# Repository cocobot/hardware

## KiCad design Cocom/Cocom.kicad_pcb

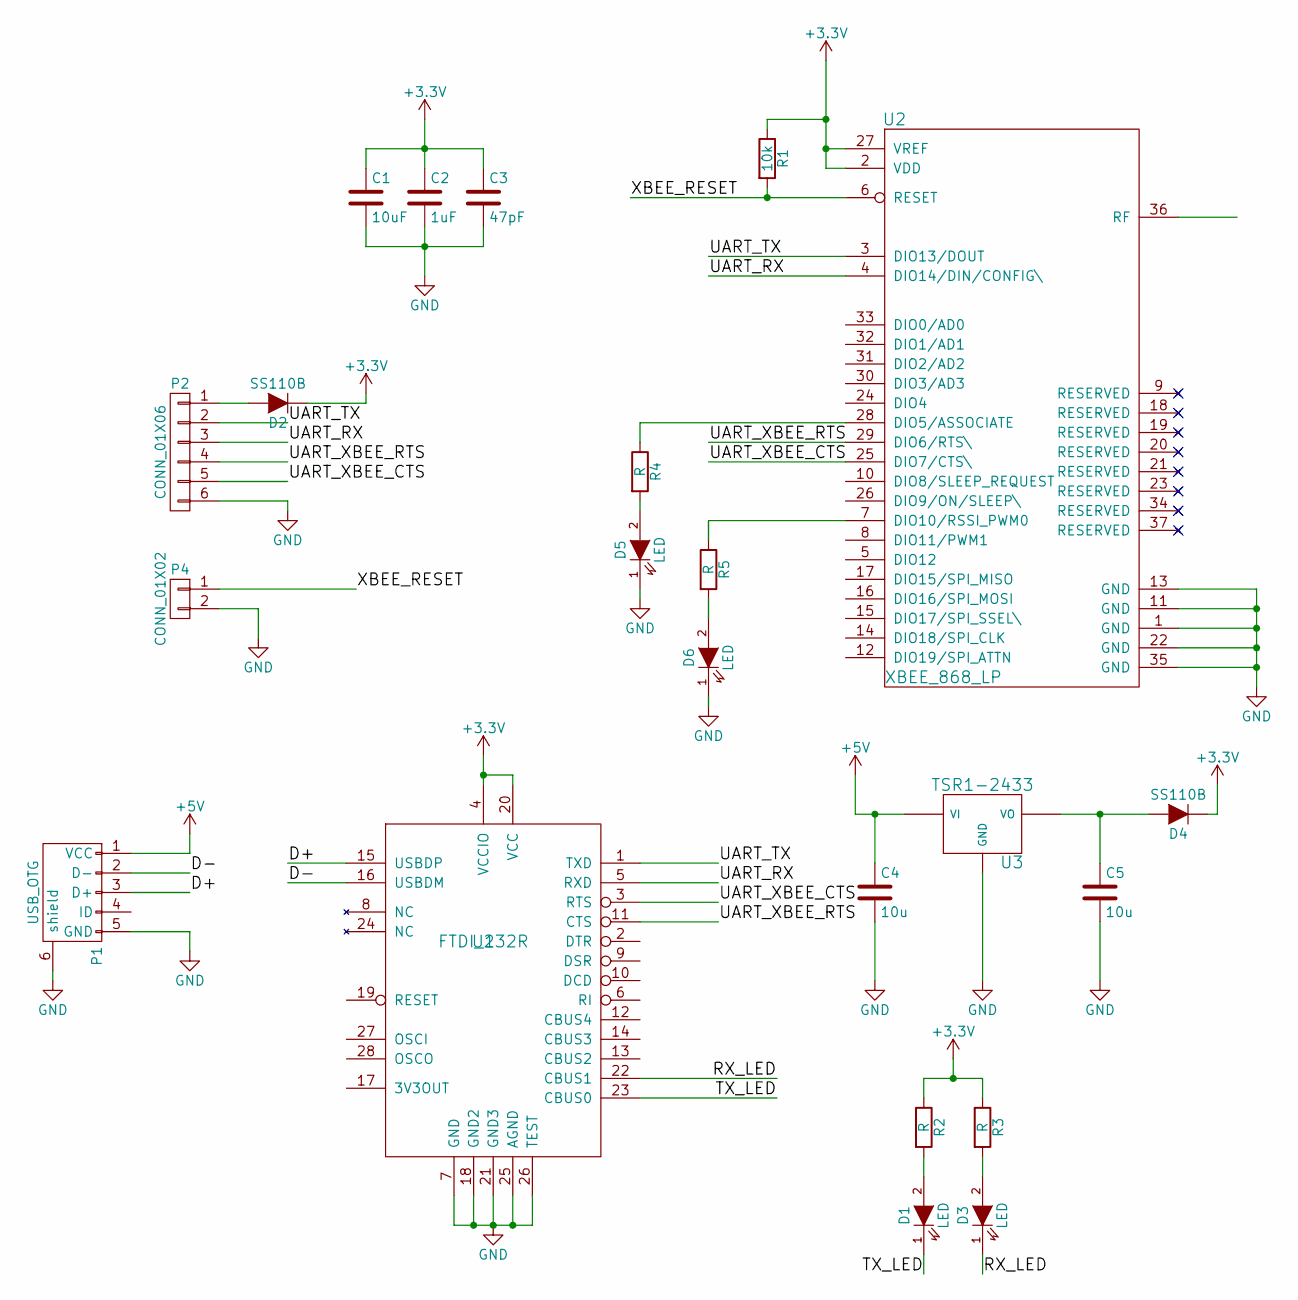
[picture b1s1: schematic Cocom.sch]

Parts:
C1: 10uF; C_0603_HandSoldering
C2: 1uF; C_0603_HandSoldering
C3: 47pF; C_0603_HandSoldering
C4, C5: 10u; C_0603_HandSoldering
D1, D3, D5, D6: LED; LED_0603
D2, D4: SS110B; SOD5336X244
P1: USB_OTG; USB_Micro-B_10103594-0001LF
P2: CONN_01X06; BM06B-SRSS-TB(LFSN)
P4: CONN_01X02; Pin_Header_Straight_1x02
R1: 10k; R_0603_HandSoldering
R2, R3, R4, R5: R; R_0603_HandSoldering
U1: FTDI_232R; SSOP-28_5.3x10.2mm_Pitch0.65mm
U2: XBEE_868_LP
U3: TSR1-2433; TSR-1

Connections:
+3V3: C1.1, C2.1, C3.1, D2.1 (K), D4.1 (K), R1.1, R2.1, R3.1, U1.4 (VCCIO), U1.20 (VCC), U2.2 (VDD), U2.27 (VREF)
+5V: C4.1, P1.1 (VCC), U3.1 (VI)
/D+: P1.3 (D+), U1.15 (USBDP)
/D-: P1.2 (D-), U1.16 (USBDM)
/RX_LED: D3.1 (K), U1.22 (CBUS1)
/TX_LED: D1.1 (K), U1.23 (CBUS0)
/UART_RX: P2.3, U1.5 (RXD), U2.4 (DIO14/DIN/CONFIG\)
/UART_TX: P2.2, U1.1 (TXD), U2.3 (DIO13/DOUT)
/UART_XBEE_CTS: P2.5, U1.3 (RTS), U2.25 (DIO7/CTS\)
/UART_XBEE_RTS: P2.4, U1.11 (CTS), U2.29 (DIO6/RTS\)
/XBEE_RESET: P4.1, R1.2, U2.6 (RESET)
GND: C1.2, C2.2, C3.2, C4.2, C5.2, D5.1 (K), D6.1 (K), P1.5 (GND), P1.6 (shield), P2.6, P4.2, U1.7 (GND), U1.18 (GND2), U1.21 (GND3), U1.25 (AGND), U1.26 (TEST), U2.1 (GND), U2.11 (GND), U2.13 (GND), U2.22 (GND), U2.35 (GND), U3.2 (GND)
unnamed: C5.1, D4.2 (A), U3.3 (VO)
unnamed: D1.2 (A), R2.2
unnamed: D2.2 (A), P2.1
unnamed: D3.2 (A), R3.2
unnamed: D5.2 (A), R4.2
unnamed: D6.2 (A), R5.2
unnamed: R4.1, U2.28 (DIO5/ASSOCIATE)
unnamed: R5.1, U2.7 (DIO10/RSSI_PWM0)

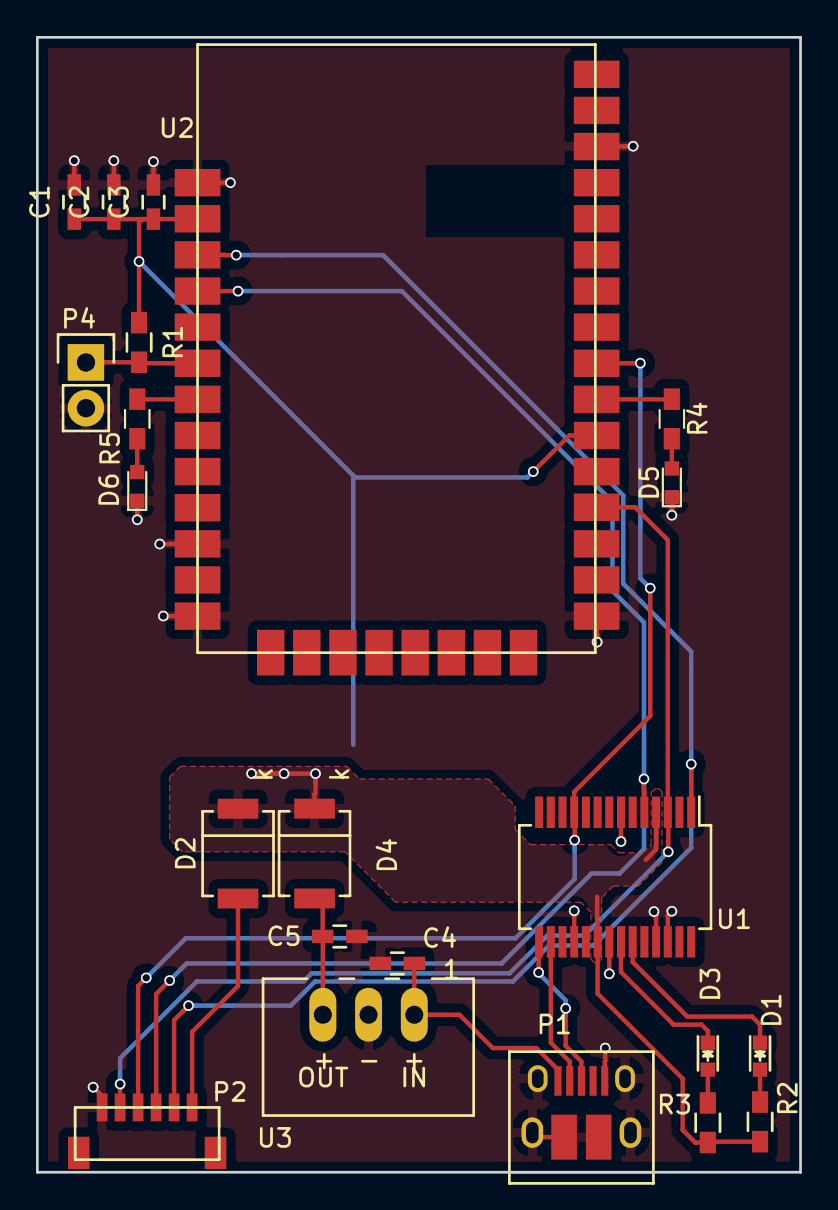
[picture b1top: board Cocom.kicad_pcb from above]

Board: 2 copper layers, 42.4 x 63.1 mm, 22 parts (0 on the bottom side), 20 nets.

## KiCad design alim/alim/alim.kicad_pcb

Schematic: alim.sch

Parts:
C1, C2, C5, C6, C8, C9: C; C_1210_HandSoldering
C3, C4: C; C_0805_HandSoldering
C7: Chimique (OSEF de la valeur et la taille, juste u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; c_elec_6.3x7.7
D1: DIODEZENER; D_SMA_Handsoldering
H1, H2, H3, H4: CONN_1
L1, L2: INDUCTOR; L_Wuerth_WE-PD4-Typ-X
P1, P2, P3, P4: CONN_2_PWR; TerminalBlock_WAGO-236_2Stift_RM5mm_2pol
P5: CONN_2_PWR; Socket_MOLEX-KK-RM2-54mm_Lock_2pin_straight
Q1, Q2, Q3, Q4: BSC046N10NS3; TDSON-8-1_HandSoldering
R1, R2, R3, R4, R5: R; R_0603_HandSoldering
U1, U2: TPS5430DDA; SOIC-8-PowerPAD

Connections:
GND: C1.1, C2.1, C5.1, C6.1, C7.2, C8.1, C9.1, D1.1 (A), H1.1, H2.1, H3.1, H4.1, P3.2, P4.2, P5.2, Q1.1, Q1.2, Q1.3, Q1.4, Q2.1, Q2.2, Q2.3, Q3.1, Q3.2, Q3.3, Q3.4, Q4.1, Q4.2, Q4.3, Q4.4, R3.2, R5.2, U1.6 (GND), U1.9 (PAD), U2.6 (GND), U2.9 (PAD)
unnamed: C1.2, C2.2, C7.1, P2.2, P3.1, Q1.5, U1.7 (VIN), U2.7 (VIN)
unnamed: C3.1, L1.1, Q3.5, U1.8 (PH)
unnamed: C3.2, U1.1 (BOOT)
unnamed: C4.1, L2.1, Q4.5, U2.8 (PH)
unnamed: C4.2, U2.1 (BOOT)
unnamed: C5.2, C8.2, L1.2, P4.1, R2.1
unnamed: C6.2, C9.2, L2.2, P5.1, R4.1
unnamed: D1.2 (K), Q2.4, R1.2
unnamed: P1.1, Q2.5
unnamed: P1.2, P2.1, R1.1
unnamed: R2.2, R3.1, U1.4 (VSENSE)
unnamed: R4.2, R5.1, U2.4 (VSENSE)

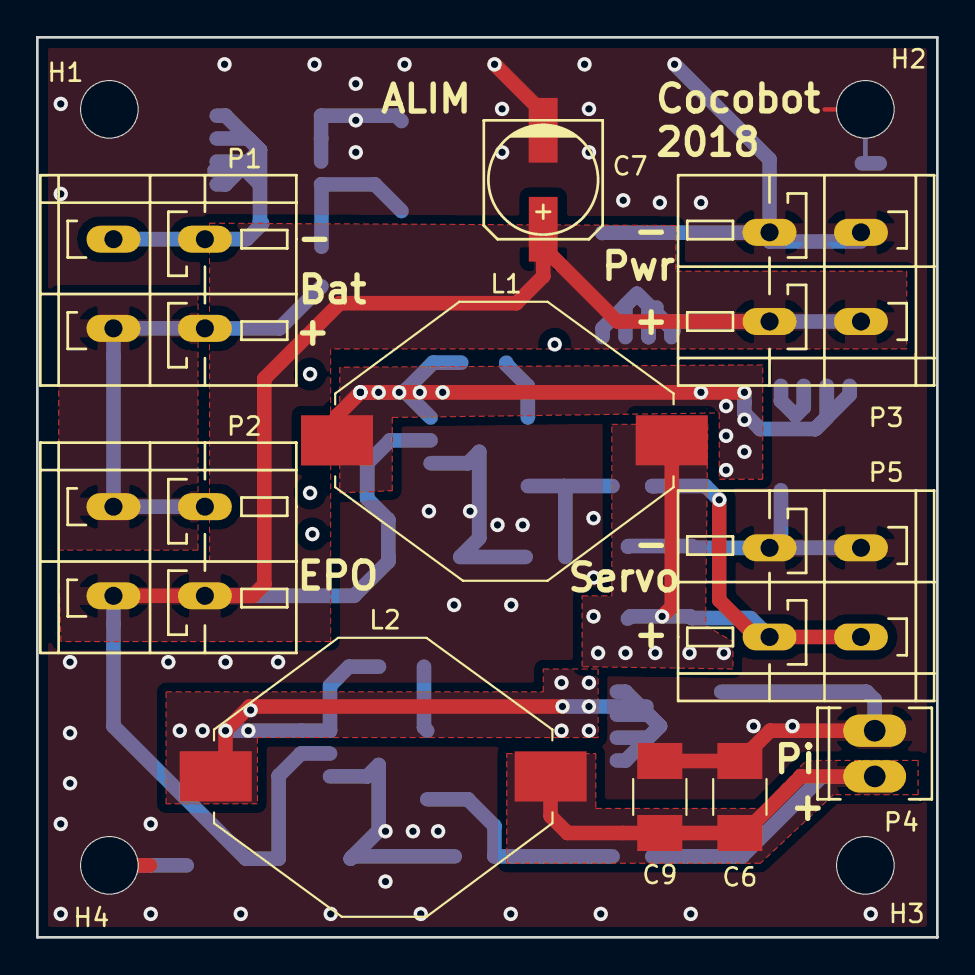
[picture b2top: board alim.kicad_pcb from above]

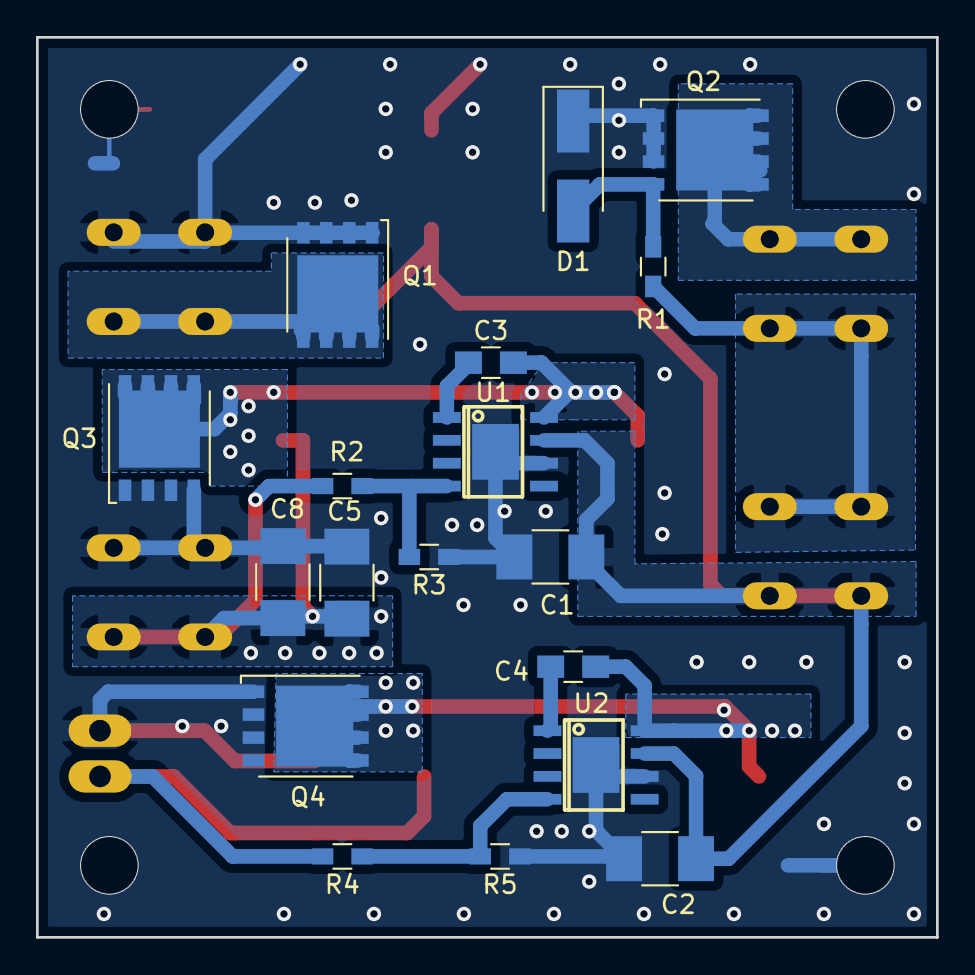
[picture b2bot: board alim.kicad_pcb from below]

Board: 2 copper layers, 50.0 x 50.0 mm, 32 parts (18 on the bottom side), 13 nets.

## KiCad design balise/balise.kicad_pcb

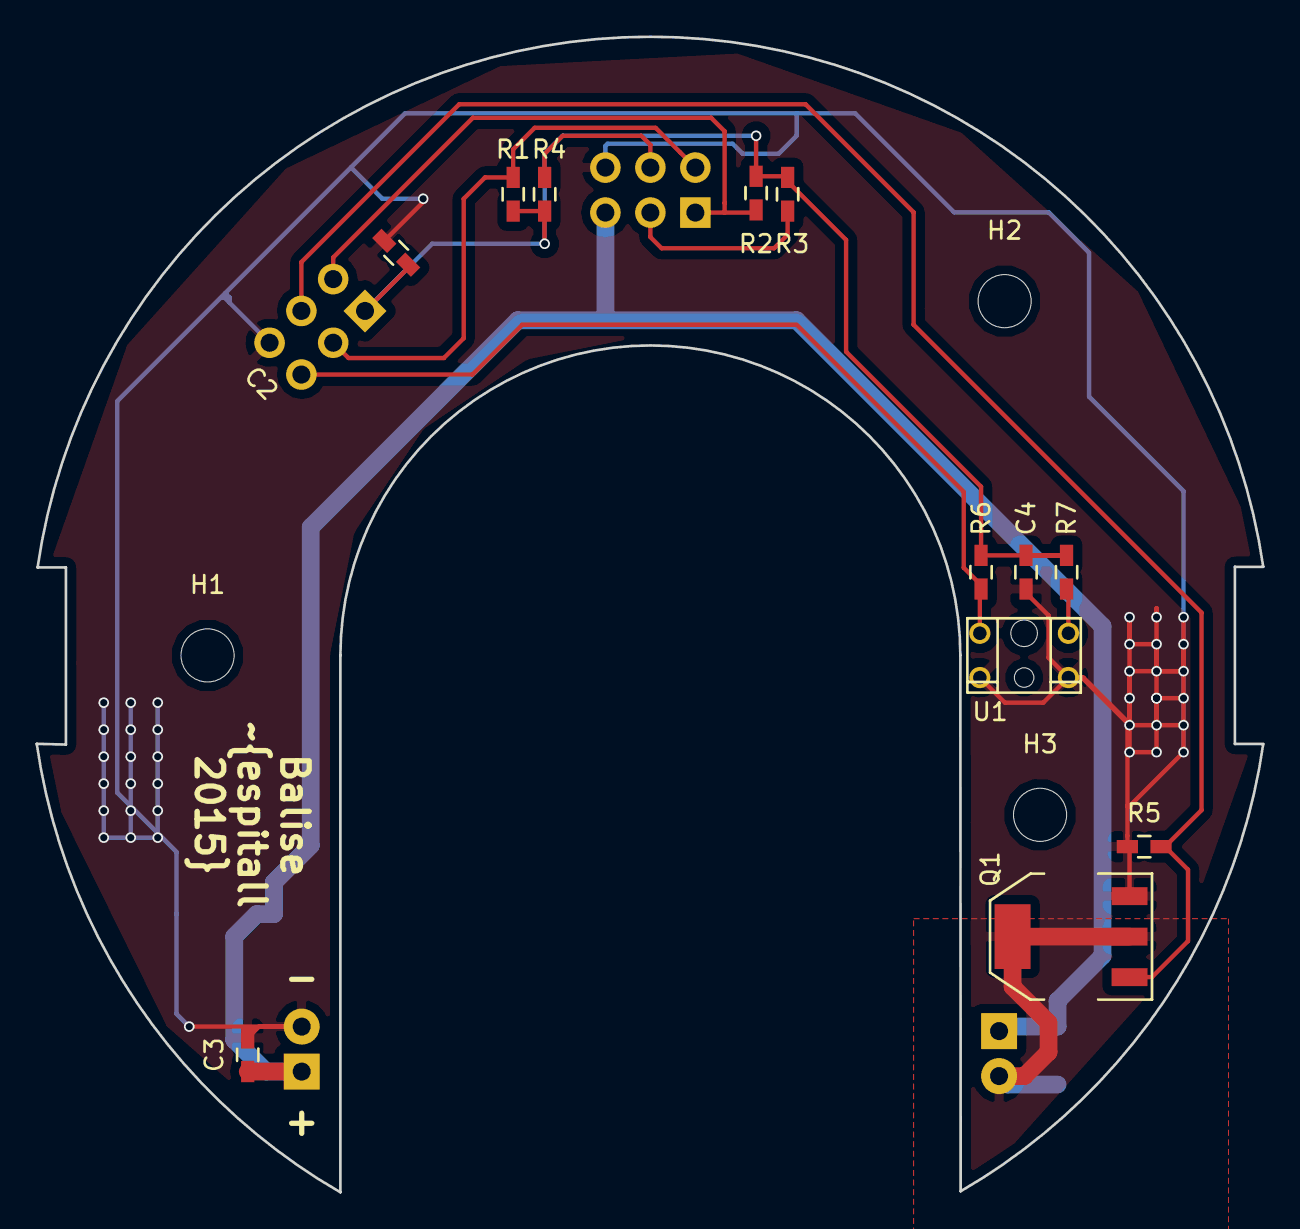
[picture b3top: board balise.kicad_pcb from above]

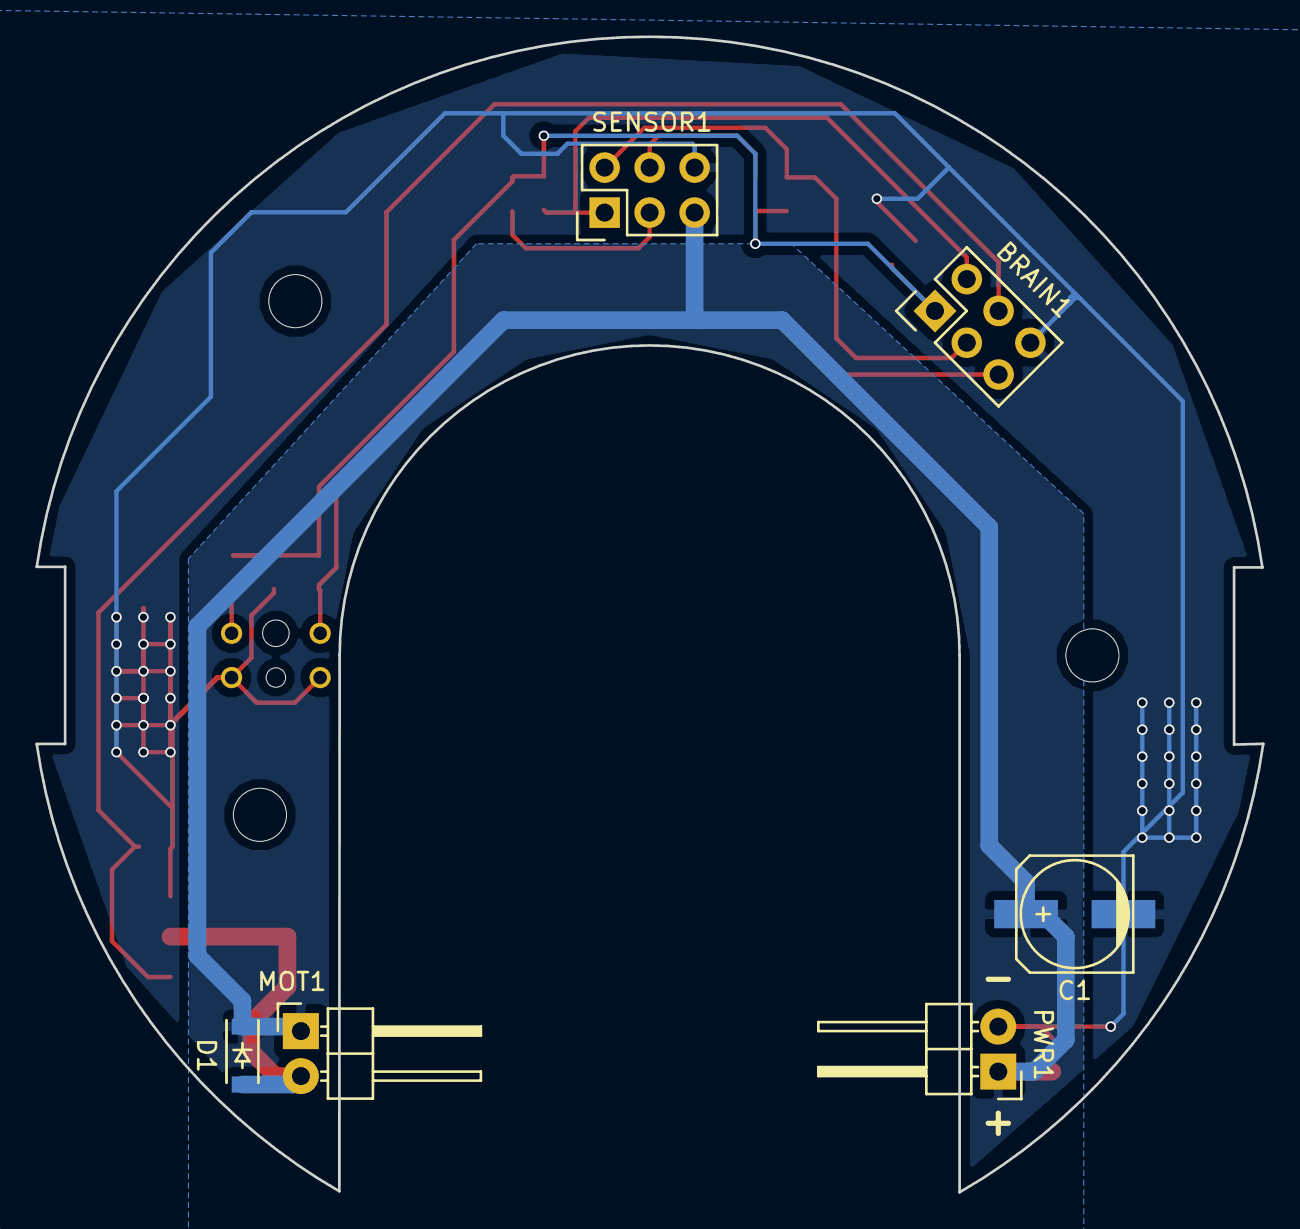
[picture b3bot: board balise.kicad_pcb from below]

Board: 2 copper layers, 69.2 x 65.2 mm, 21 parts (6 on the bottom side), 11 nets.

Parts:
BRAIN1: CONN_01X06; Pin_Header_Straight_2x03
C1: 100u; c_elec_6.3x7.7
C2, C3, C4: 100n; C_0603_HandSoldering
D1: CGRM4004-G; SOD-123
H1, H2, H3: CONN_01X01; MountingHole_3mm
MOT1: CONN_01X02; Pin_Header_Angled_1x02
PWR1: CONN_01X02; Pin_Header_Angled_1x02
Q1: DMN6068SE; SOT-223
R1, R2: 1k; C_0603_HandSoldering
R3, R4: 220; C_0603_HandSoldering
R5: 10k; C_0603_HandSoldering
R6: 270; C_0603_HandSoldering
R7: 100; C_0603_HandSoldering
SENSOR1: CONN_01X06; Pin_Header_Straight_2x03
U1: EE-SX1106

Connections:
+3V3: BRAIN1.1, C2.1, C4.1, R1.2, R2.2, R3.2, R4.1, R6.2, R7.2
+BATT: C1.1, C3.1, D1.1, MOT1.1, PWR1.1, SENSOR1.5
/LR_LED: R3.1, SENSOR1.3
/LR_OUT_3v3: BRAIN1.2, R2.1, SENSOR1.1
/PWM_3v3: BRAIN1.4, Q1.1, R5.2
/SR_LED: R4.2, SENSOR1.4
/SR_OUT_3v3: BRAIN1.3, R1.1, SENSOR1.2
/TOP_3v3: BRAIN1.5, R6.1, U1.C
GND: BRAIN1.6, C1.2, C2.2, C3.2, C4.2, PWR1.2, Q1.3, R5.1, SENSOR1.6, U1.E, U1.K
unnamed: D1.2, MOT1.2, Q1.2, Q1.4
unnamed: R7.1, U1.A

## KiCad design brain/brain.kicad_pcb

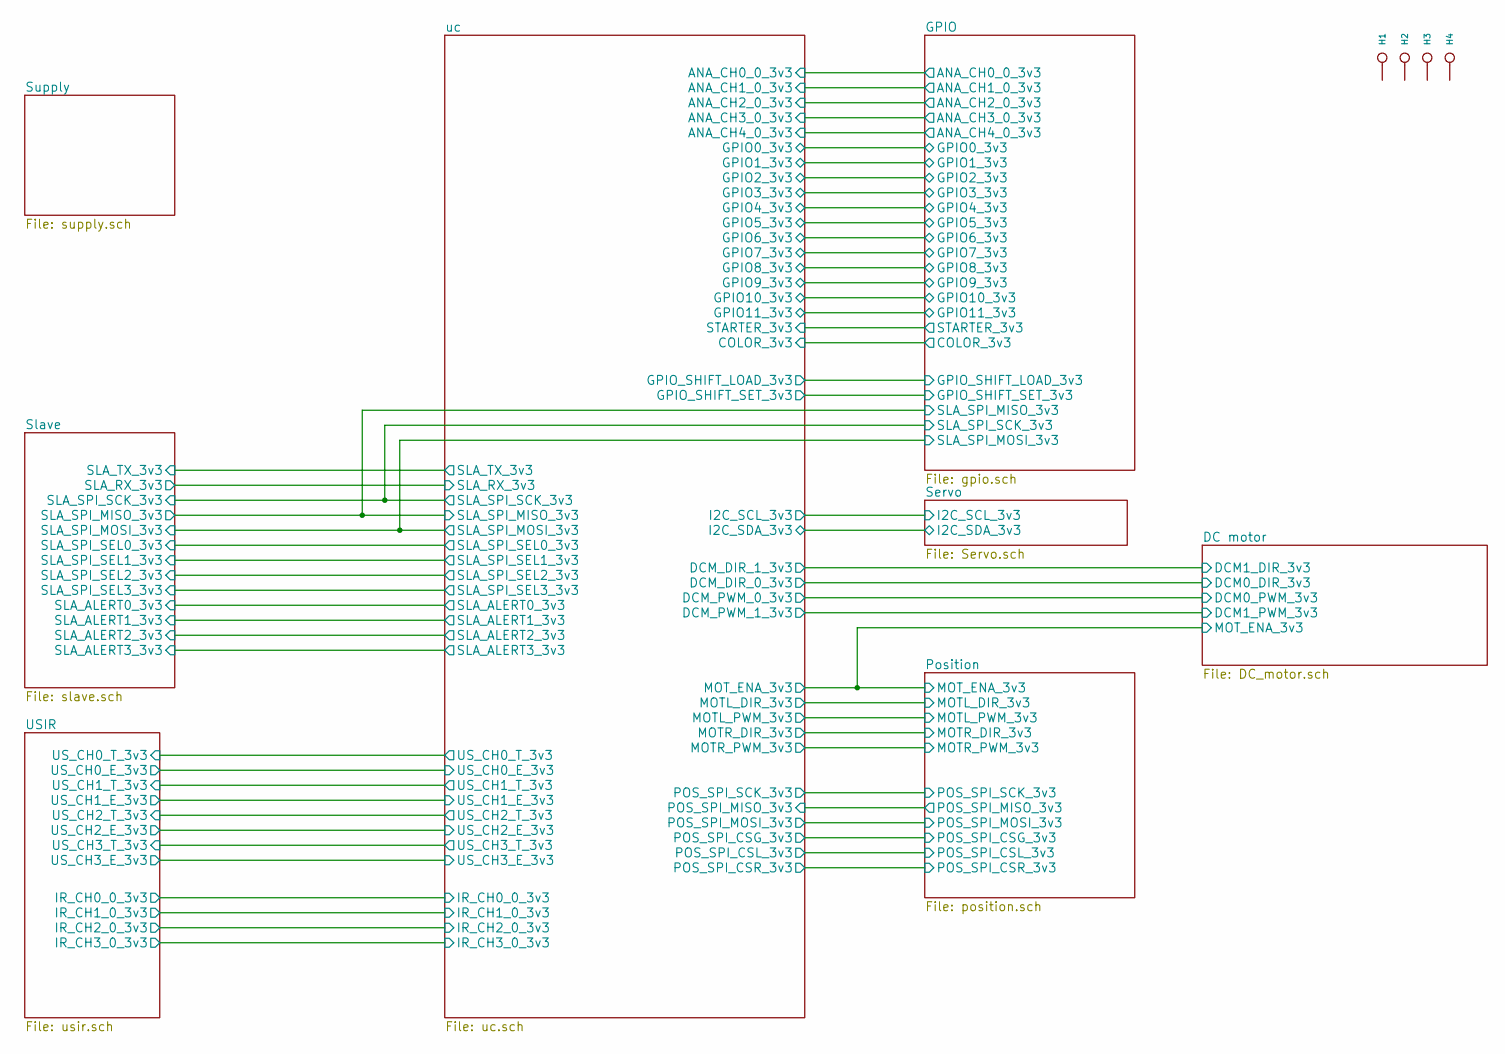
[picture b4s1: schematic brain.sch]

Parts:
H1, H2, H3, H4: CONN_1; MountingHole_3.2mm_M3

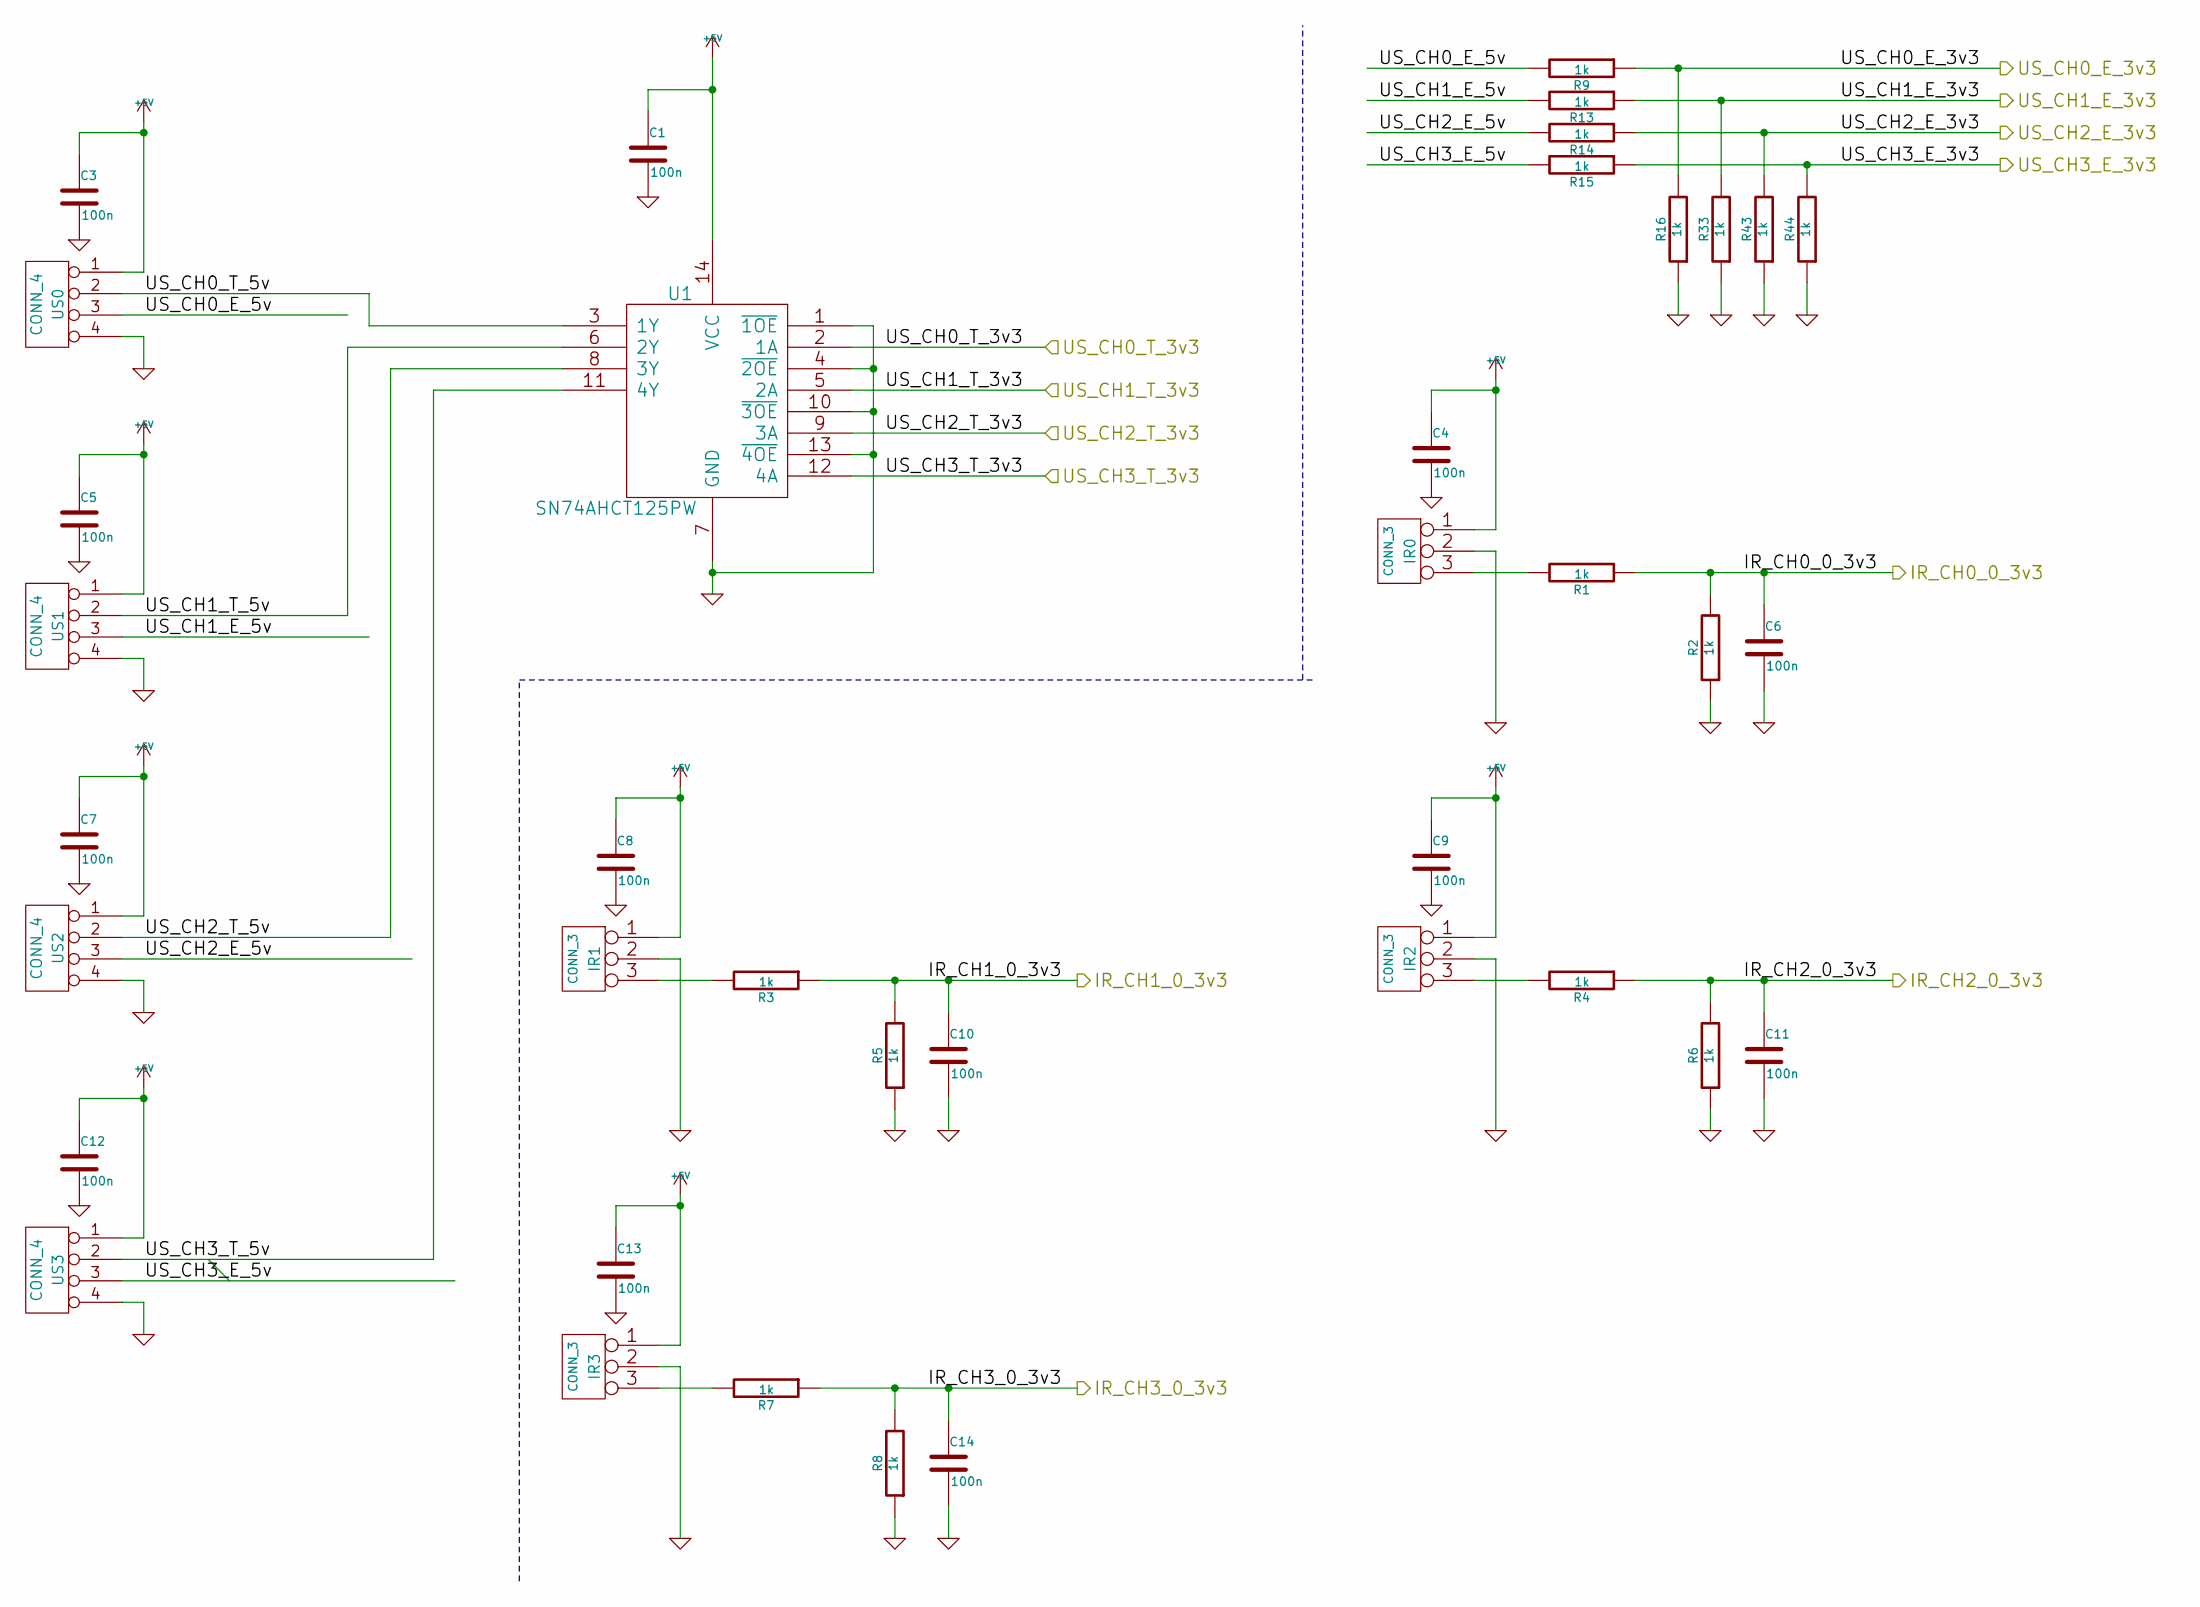
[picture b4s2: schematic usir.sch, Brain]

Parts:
C1, C3, C4, C5, C6, C7, C8, C9, C10, C11, C12, C13, C14: 100n; C_0603
IR0, IR1, IR2, IR3: CONN_3; Socket_MOLEX-KK-RM2-54mm_Lock_3pin_straight
R1, R2, R3, R4, R5, R6, R7, R8, R9, R13, R14, R15, R16, R33, R43, R44: 1k; R_0603
U1: SN74AHCT125PW; TSSOP-14_4.4x5mm_Pitch0.65mm
US0, US1, US2, US3: CONN_4; Socket_MOLEX-KK-RM2-54mm_Lock_4pin_straight

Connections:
+5V: C1.1, C3.1, C4.1, C5.1, C7.1, C8.1, C9.1, C12.1, C13.1, IR0.1, IR1.1, IR2.1, IR3.1, U1.14 (VCC), US0.1, US1.1, US2.1, US3.1; also elsewhere on the board
/USIR/IR_CH0_0_3v3: C6.1, R1.1, R2.2; also elsewhere on the board
/USIR/IR_CH1_0_3v3: C10.1, R3.1, R5.2; also elsewhere on the board
/USIR/IR_CH2_0_3v3: C11.1, R4.1, R6.2; also elsewhere on the board
/USIR/IR_CH3_0_3v3: C14.1, R7.1, R8.2; also elsewhere on the board
/USIR/US_CH0_E_3v3: R9.1, R16.2; also elsewhere on the board
/USIR/US_CH0_E_5v: R9.2, US0.3
/USIR/US_CH0_T_3v3: U1.2 (1A); also elsewhere on the board
/USIR/US_CH0_T_5v: U1.3 (1Y), US0.2
/USIR/US_CH1_E_3v3: R13.1, R33.2; also elsewhere on the board
/USIR/US_CH1_E_5v: R13.2, US1.3
/USIR/US_CH1_T_3v3: U1.5 (2A); also elsewhere on the board
/USIR/US_CH1_T_5v: U1.6 (2Y), US1.2
/USIR/US_CH2_E_3v3: R14.1, R43.2; also elsewhere on the board
/USIR/US_CH2_E_5v: R14.2, US2.3
/USIR/US_CH2_T_3v3: U1.9 (3A); also elsewhere on the board
/USIR/US_CH2_T_5v: U1.8 (3Y), US2.2
/USIR/US_CH3_E_3v3: R15.1, R44.2; also elsewhere on the board
/USIR/US_CH3_E_5v: R15.2, US3.3
/USIR/US_CH3_T_3v3: U1.12 (4A); also elsewhere on the board
/USIR/US_CH3_T_5v: U1.11 (4Y), US3.2
GND: C1.2, C3.2, C4.2, C5.2, C6.2, C7.2, C8.2, C9.2, C10.2, C11.2, C12.2, C13.2, C14.2, IR0.2 (PM), IR1.2 (PM), IR2.2 (PM), IR3.2 (PM), R2.1, R5.1, R6.1, R8.1, R16.1, R33.1, R43.1, R44.1, U1.1 (~1OE), U1.4 (~2OE), U1.7 (GND), U1.10 (~3OE), U1.13 (~4OE), US0.4, US1.4, US2.4, US3.4; also elsewhere on the board
unnamed: IR0.3, R1.2
unnamed: IR1.3, R3.2
unnamed: IR2.3, R4.2
unnamed: IR3.3, R7.2

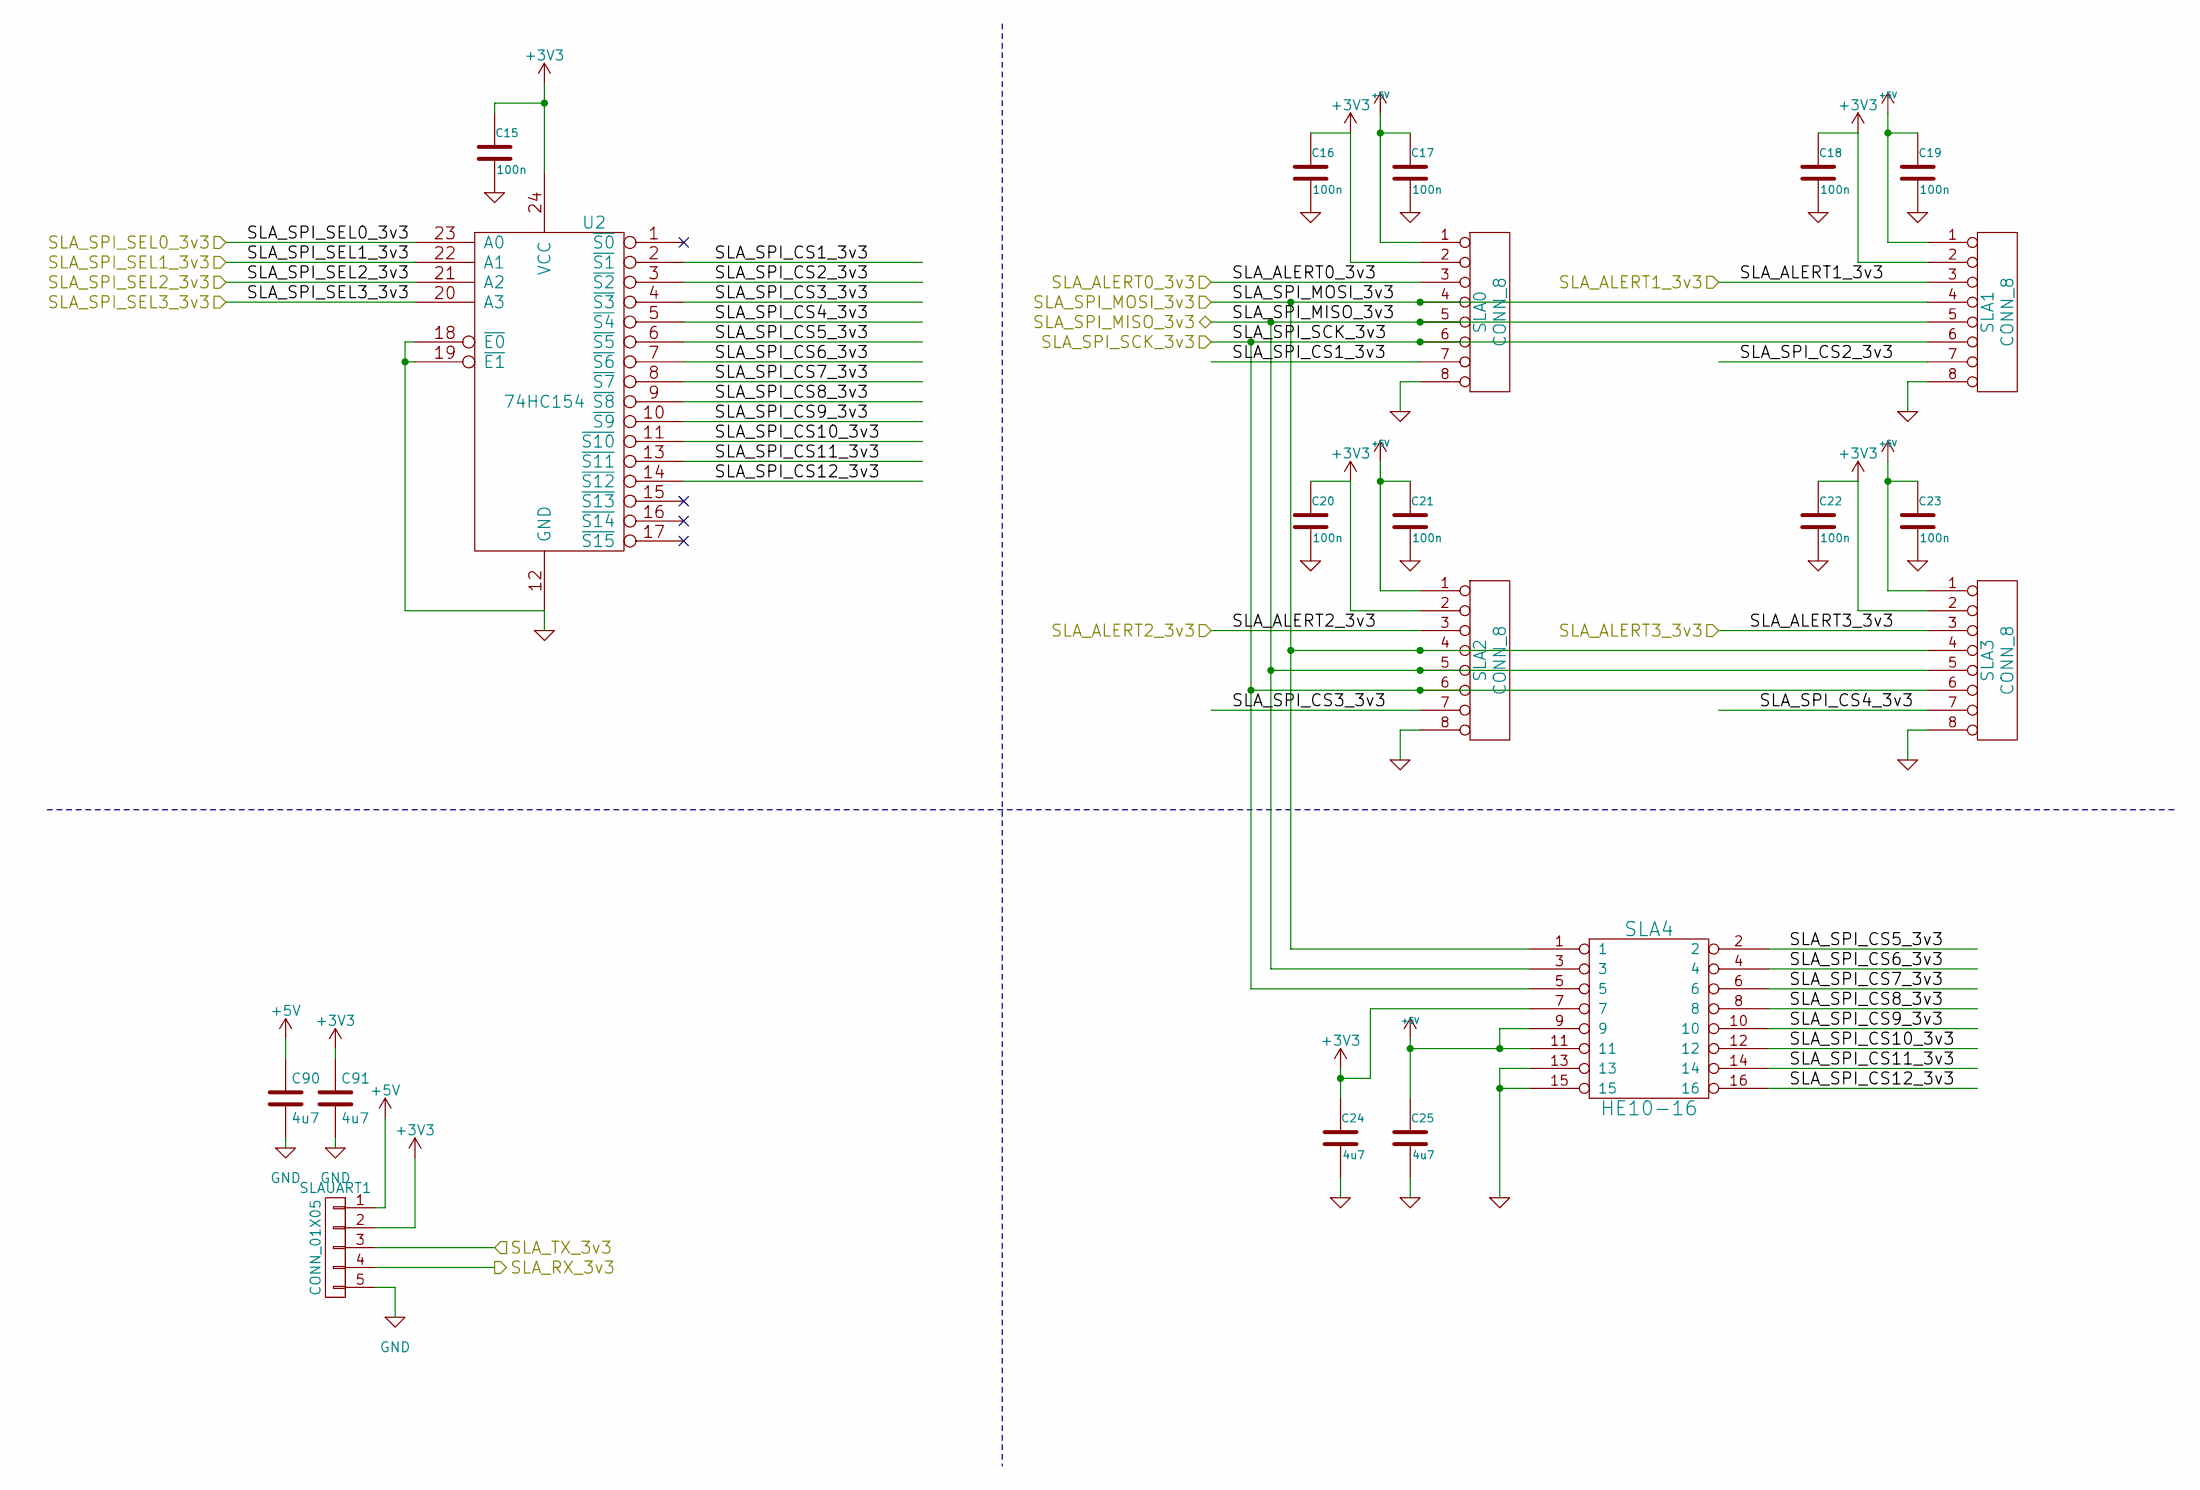
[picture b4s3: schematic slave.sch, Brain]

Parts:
C15, C16, C17, C18, C19, C20, C21, C22, C23: 100n; C_0603
C24, C25, C90, C91: 4u7; C_0603
SLA0, SLA1, SLA2, SLA3: CONN_8; Socket_MOLEX-KK-RM2-54mm_Lock_8pin_straight
SLA4: HE10-16; HE10_16D
SLAUART1: CONN_01X05; Socket_MOLEX-KK-RM2-54mm_Lock_5pin_straight
U2: 74HC154; SOIC-24_7.5x15.4mm_Pitch1.27mm

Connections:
+3V3: C15.1, C16.1, C18.1, C20.1, C22.1, C24.1, C91.1, SLA0.2, SLA1.2, SLA2.2, SLA3.2, SLA4.7, SLAUART1.2, U2.24 (VCC); also elsewhere on the board
+5V: C17.1, C19.1, C21.1, C23.1, C25.1, C90.1, SLA0.1, SLA1.1, SLA2.1, SLA3.1, SLA4.9, SLA4.11, SLAUART1.1; also elsewhere on the board
/GPIO/SLA_SPI_MISO_3v3: SLA0.5, SLA1.5, SLA2.5, SLA3.5, SLA4.3; also elsewhere on the board
/GPIO/SLA_SPI_MOSI_3v3: SLA0.4, SLA1.4, SLA2.4, SLA3.4, SLA4.1; also elsewhere on the board
/GPIO/SLA_SPI_SCK_3v3: SLA0.6, SLA1.6, SLA2.6, SLA3.6, SLA4.5; also elsewhere on the board
/Slave/SLA_ALERT0_3v3: SLA0.3; also elsewhere on the board
/Slave/SLA_ALERT1_3v3: SLA1.3; also elsewhere on the board
/Slave/SLA_ALERT2_3v3: SLA2.3; also elsewhere on the board
/Slave/SLA_ALERT3_3v3: SLA3.3; also elsewhere on the board
/Slave/SLA_RX_3v3: SLAUART1.4; also elsewhere on the board
/Slave/SLA_SPI_CS1_3v3: SLA0.7, U2.2 (~S1)
/Slave/SLA_SPI_CS2_3v3: SLA1.7, U2.3 (~S2)
/Slave/SLA_SPI_CS3_3v3: SLA2.7, U2.4 (~S3)
/Slave/SLA_SPI_CS4_3v3: SLA3.7, U2.5 (~S4)
/Slave/SLA_SPI_CS5_3v3: SLA4.2, U2.6 (~S5)
/Slave/SLA_SPI_CS6_3v3: SLA4.4, U2.7 (~S6)
/Slave/SLA_SPI_CS7_3v3: SLA4.6, U2.8 (~S7)
/Slave/SLA_SPI_CS8_3v3: SLA4.8, U2.9 (~S8)
/Slave/SLA_SPI_CS9_3v3: SLA4.10, U2.10 (~S9)
/Slave/SLA_SPI_CS10_3v3: SLA4.12, U2.11 (~S10)
/Slave/SLA_SPI_CS11_3v3: SLA4.14, U2.13 (~S11)
/Slave/SLA_SPI_CS12_3v3: SLA4.16, U2.14 (~S12)
/Slave/SLA_SPI_SEL0_3v3: U2.23 (A0); also elsewhere on the board
/Slave/SLA_SPI_SEL1_3v3: U2.22 (A1); also elsewhere on the board
/Slave/SLA_SPI_SEL2_3v3: U2.21 (A2); also elsewhere on the board
/Slave/SLA_SPI_SEL3_3v3: U2.20 (A3); also elsewhere on the board
/Slave/SLA_TX_3v3: SLAUART1.3; also elsewhere on the board
GND: C15.2, C16.2, C17.2, C18.2, C19.2, C20.2, C21.2, C22.2, C23.2, C24.2, C25.2, C90.2, C91.2, SLA0.8, SLA1.8, SLA2.8, SLA3.8, SLA4.13, SLA4.15, SLAUART1.5, U2.12 (GND), U2.18 (~E0), U2.19 (~E1); also elsewhere on the board
